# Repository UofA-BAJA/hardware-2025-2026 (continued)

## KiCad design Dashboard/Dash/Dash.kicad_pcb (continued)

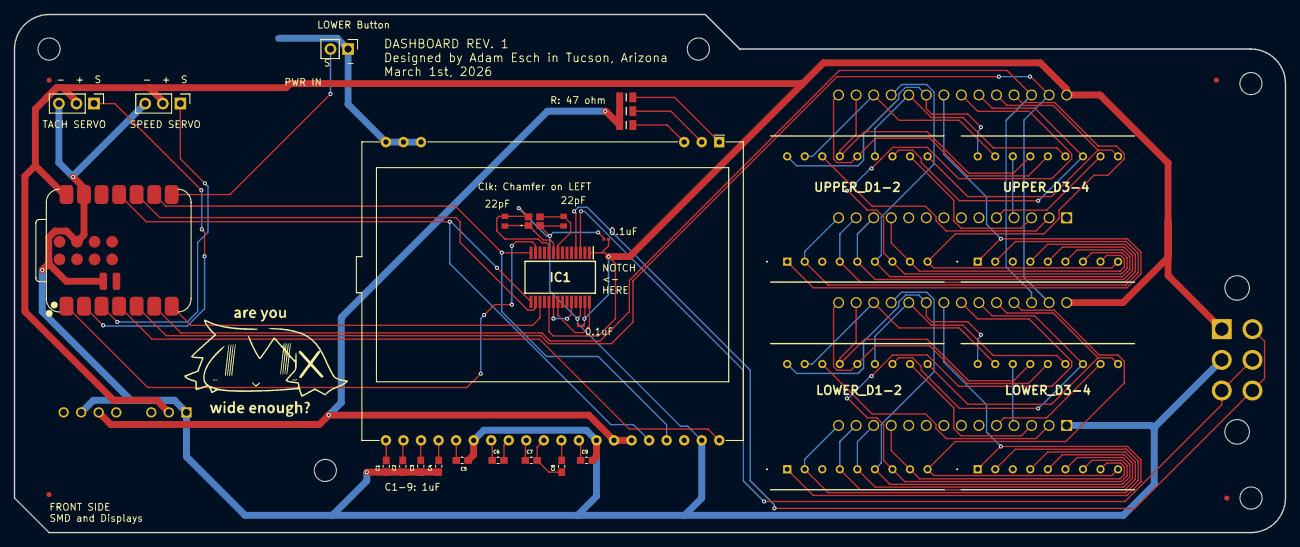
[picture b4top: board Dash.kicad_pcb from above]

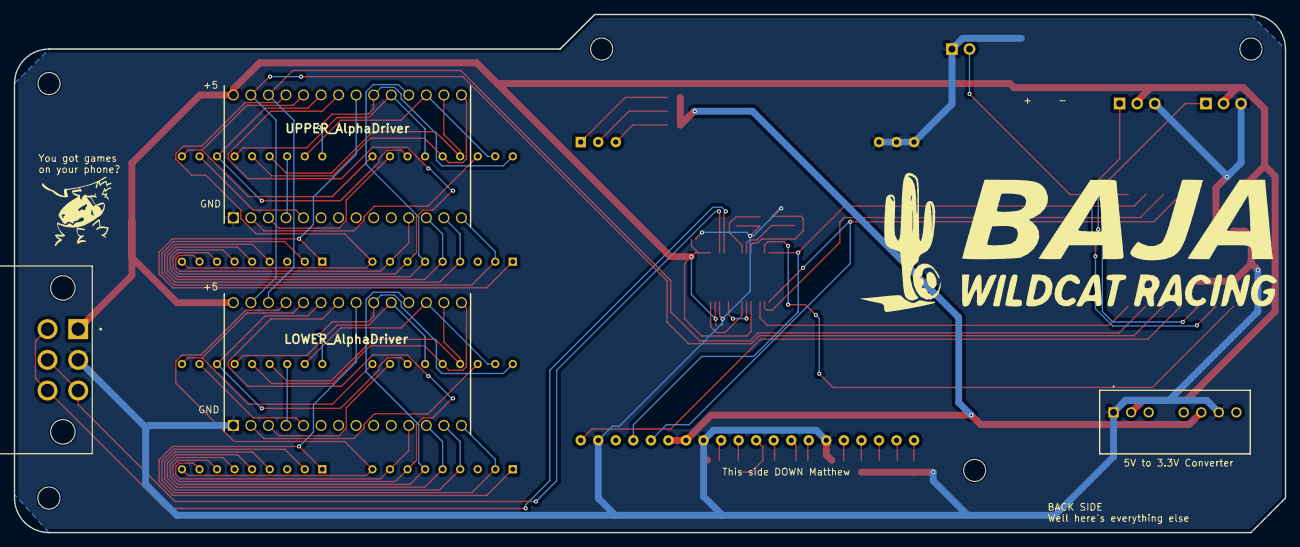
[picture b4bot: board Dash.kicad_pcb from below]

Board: 2 copper layers, 184.0 x 75.0 mm, 31 parts (4 on the bottom side), 72 nets.

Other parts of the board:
LOWER_AlphaDriver: Alphanumeric Driver LOWER; DIP1778W100P254L3556H630Q28N
UPPER_AlphaDriver: Alphanumeric Driver UPPER; DIP1778W100P254L3556H630Q28N

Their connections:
+5V: LOWER_AlphaDriver.28 (VDD), UPPER_AlphaDriver.28 (VDD); also elsewhere on the board
COM_Digit1_LOWER: LOWER_AlphaDriver.2 (C0); also elsewhere on the board
COM_Digit1_UPPER: UPPER_AlphaDriver.2 (C0); also elsewhere on the board
COM_Digit2_LOWER: LOWER_AlphaDriver.3 (C1); also elsewhere on the board
COM_Digit2_UPPER: UPPER_AlphaDriver.3 (C1); also elsewhere on the board
COM_Digit3_LOWER: LOWER_AlphaDriver.4 (C2); also elsewhere on the board
COM_Digit3_UPPER: UPPER_AlphaDriver.4 (C2); also elsewhere on the board
COM_Digit4_LOWER: LOWER_AlphaDriver.5 (C3); also elsewhere on the board
COM_Digit4_UPPER: UPPER_AlphaDriver.5 (C3); also elsewhere on the board
GND: LOWER_AlphaDriver.1 (GND), UPPER_AlphaDriver.1 (GND); also elsewhere on the board
ROW0_LOWER: LOWER_AlphaDriver.23 (A2); also elsewhere on the board
ROW0_UPPER: UPPER_AlphaDriver.23 (A2); also elsewhere on the board
ROW1_LOWER: LOWER_AlphaDriver.24 (A1); also elsewhere on the board
ROW1_UPPER: UPPER_AlphaDriver.24 (A1); also elsewhere on the board
ROW2_LOWER: LOWER_AlphaDriver.25 (A0); also elsewhere on the board
ROW2_UPPER: UPPER_AlphaDriver.25 (A0); also elsewhere on the board
ROW3_LOWER: LOWER_AlphaDriver.22 (A3); also elsewhere on the board
ROW3_UPPER: UPPER_AlphaDriver.22 (A3); also elsewhere on the board
ROW4_LOWER: LOWER_AlphaDriver.21 (A4); also elsewhere on the board
ROW4_UPPER: UPPER_AlphaDriver.21 (A4); also elsewhere on the board
ROW5_LOWER: LOWER_AlphaDriver.20 (A5); also elsewhere on the board
ROW5_UPPER: UPPER_AlphaDriver.20 (A5); also elsewhere on the board
ROW6_LOWER: LOWER_AlphaDriver.19 (A6); also elsewhere on the board
ROW6_UPPER: UPPER_AlphaDriver.19 (A6); also elsewhere on the board
ROW7_LOWER: LOWER_AlphaDriver.18 (A7); also elsewhere on the board
ROW7_UPPER: UPPER_AlphaDriver.18 (A7); also elsewhere on the board
ROW8_LOWER: LOWER_AlphaDriver.17 (A8); also elsewhere on the board
ROW8_UPPER: UPPER_AlphaDriver.17 (A8); also elsewhere on the board
ROW9_LOWER: LOWER_AlphaDriver.16 (A9); also elsewhere on the board
ROW9_UPPER: UPPER_AlphaDriver.16 (A9); also elsewhere on the board
ROW10_LOWER: LOWER_AlphaDriver.15 (A10); also elsewhere on the board
ROW10_UPPER: UPPER_AlphaDriver.15 (A10); also elsewhere on the board
ROW11_LOWER: LOWER_AlphaDriver.14 (A11); also elsewhere on the board
ROW11_UPPER: UPPER_AlphaDriver.14 (A11); also elsewhere on the board
ROW12_LOWER: LOWER_AlphaDriver.13 (A12); also elsewhere on the board
ROW12_UPPER: UPPER_AlphaDriver.13 (A12); also elsewhere on the board
ROW13_LOWER: LOWER_AlphaDriver.12 (A13); also elsewhere on the board
ROW13_UPPER: UPPER_AlphaDriver.12 (A13); also elsewhere on the board
ROW14_LOWER: LOWER_AlphaDriver.11 (A14); also elsewhere on the board
ROW14_UPPER: UPPER_AlphaDriver.11 (A14); also elsewhere on the board
SCL: LOWER_AlphaDriver.26 (SCL), UPPER_AlphaDriver.26 (SCL); also elsewhere on the board
SDA: LOWER_AlphaDriver.27 (SDA), UPPER_AlphaDriver.27 (SDA); also elsewhere on the board

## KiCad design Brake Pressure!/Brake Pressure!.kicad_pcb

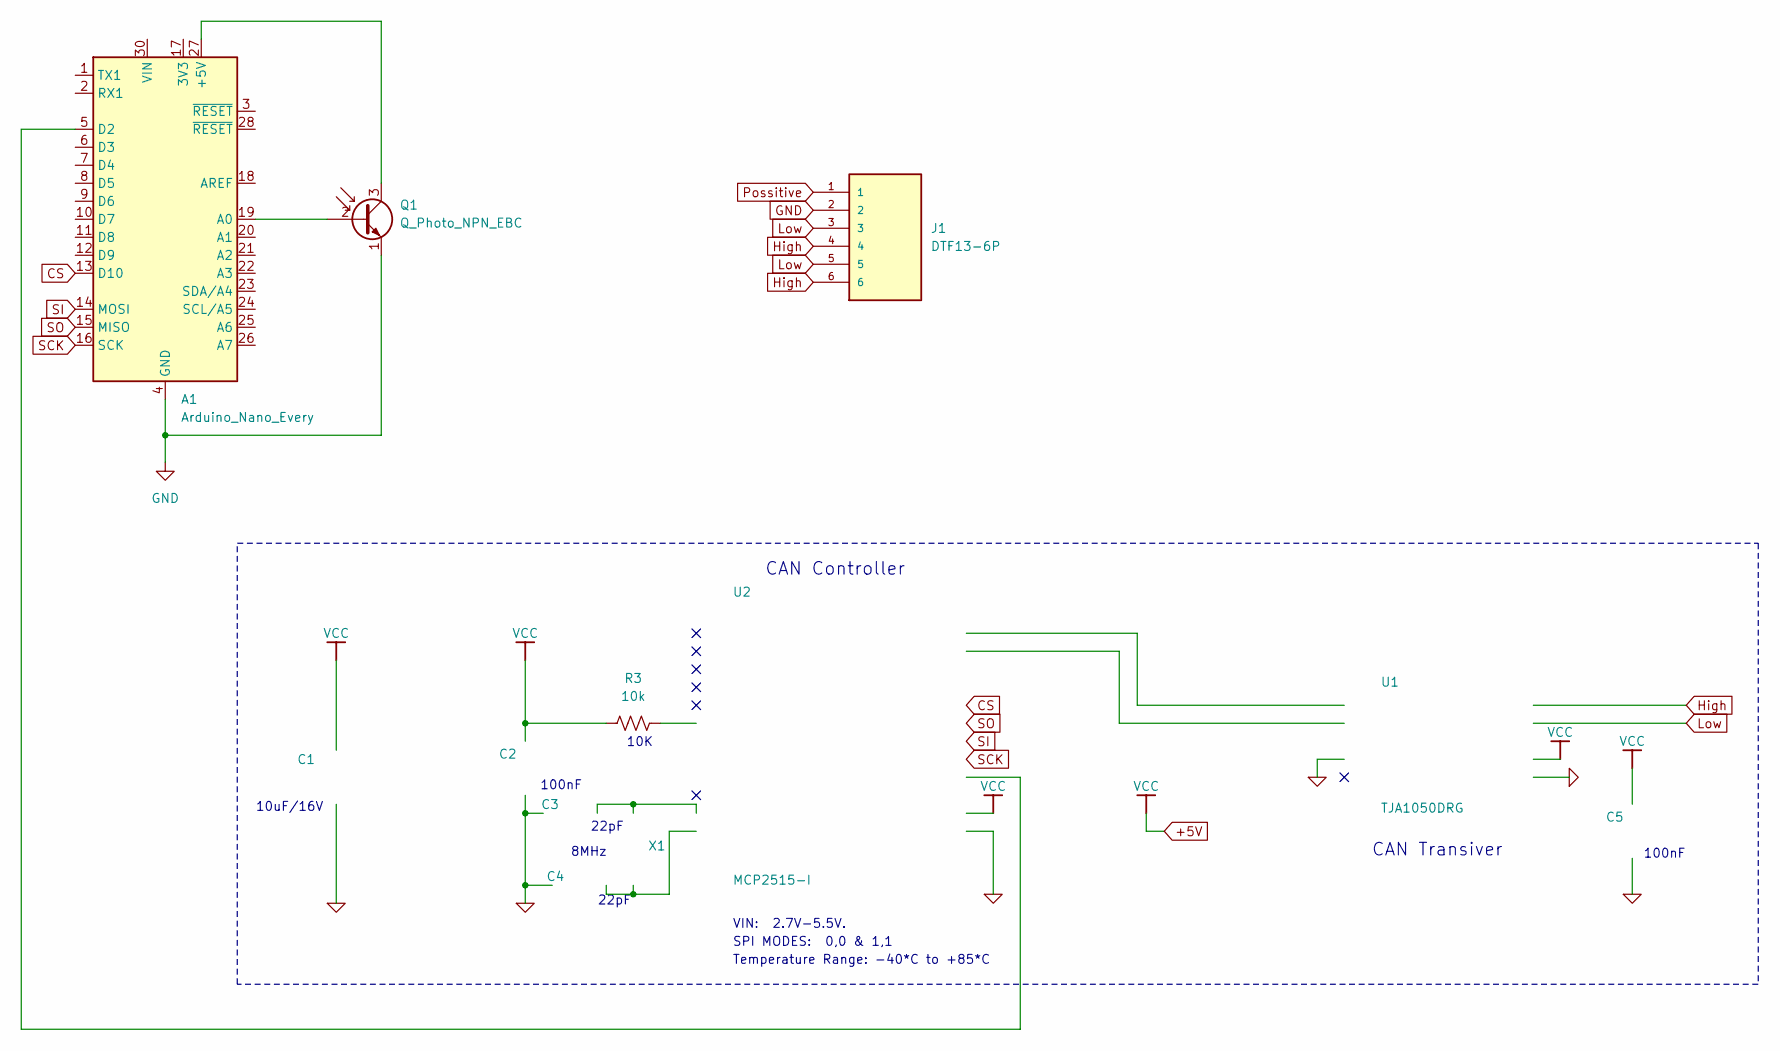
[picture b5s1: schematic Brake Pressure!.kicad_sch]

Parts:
A1: Arduino_Nano_Every; Arduino_Nano
C1: 10uF/16V; CP_EIA-1608-08_AVX-J
C2, C5: 100nF; C_0603_1608Metric; PART NUMBER C0603-N.C.
C3, C4: 22pF; C_0603_1608Metric; PART NUMBER C0603-N.C.
J1: DTF13-6P; TE_DTF13-6P; PARTREV B
Q1: Q_Photo_NPN_EBC; TO-3P-3_Vertical
R3: 10k; R_Axial_DIN0204_L3.6mm_D1.6mm_P7.62mm_Horizontal
U1: TJA1050DRG; SOIC-8_5.3x5.3mm_P1.27mm; MANUFACTURER PART TJA1050DRG; LCSC PART NAME TJA1050DRG
U2: MCP2515-I; SOIC-18W_7.5x11.6mm_P1.27mm; MANUFACTURER PART MCP2515-I; JLCPCB PART CLASS Extended Part
X1: 8MHz; Crystal_SMD_HC49-SD

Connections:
0: C1.2, C2.1, C3.2, C4.2, C5.1, U1.2 (GND), U1.8 (STB), U2.9 (VSS)
+5V: C1.1, C2.2, C5.2, R3.1, U1.3 (VCC), U2.18 (VDD)
CS: A1.13 (D10), U2.16 (~CS)
GND: A1.4 (GND), A1.29 (GND), J1.2, Q1.1 (E)
High: J1.4, J1.6, U1.7 (CANH)
Low: J1.3, J1.5, U1.6 (CANL)
unnamed: A1.27 (+5V), Q1.3 (C)
unnamed: A1.19 (A0), Q1.2 (B)
unnamed: A1.5 (D2), U2.12 (~INT)
unnamed: U1.4 (RXD), U2.2 (RXCAN)
unnamed: U1.1 (TXD), U2.1 (TXCAN)
unnamed: C4.1, U2.8 (OSC1), X1.1
unnamed: C3.1, U2.7 (OSC2), X1.2
unnamed: R3.2, U2.17 (~RESET)
Possitive: J1.1
SCK: A1.16 (SCK), U2.13 (SCK)
SI: A1.14 (MOSI), U2.14 (SI)
SO: A1.15 (MISO), U2.15 (SO)

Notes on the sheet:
CAN Transiver
22pF
100nF
VIN: 2.7V-5.5V.
CAN Controller
10K
Temperature Range: -40*C to +85*C
8MHz
10uF/16V
SPI MODES: 0,0 & 1,1

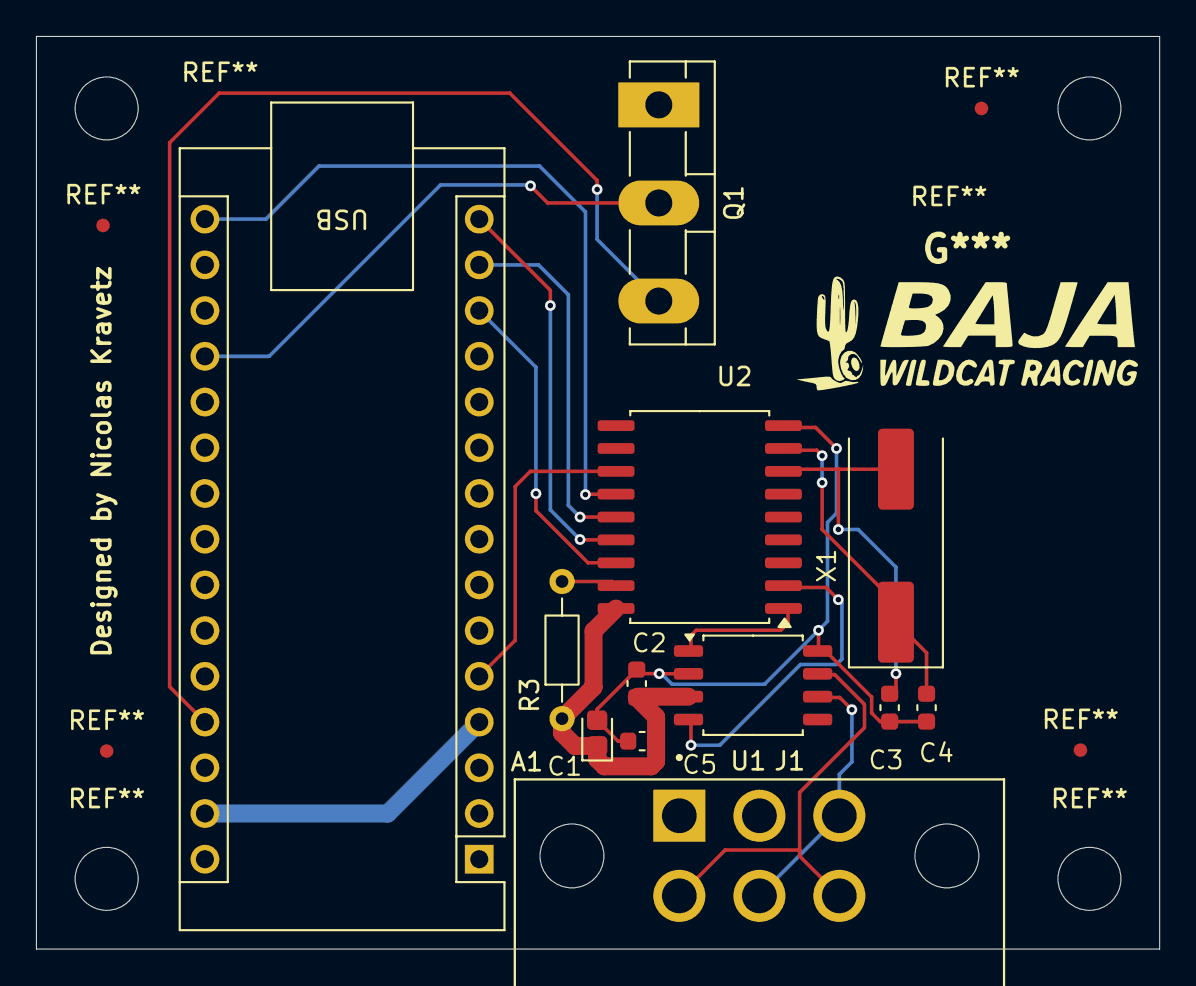
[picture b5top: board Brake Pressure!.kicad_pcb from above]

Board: 2 copper layers, 62.4 x 50.7 mm, 12 parts (0 on the bottom side), 17 nets.

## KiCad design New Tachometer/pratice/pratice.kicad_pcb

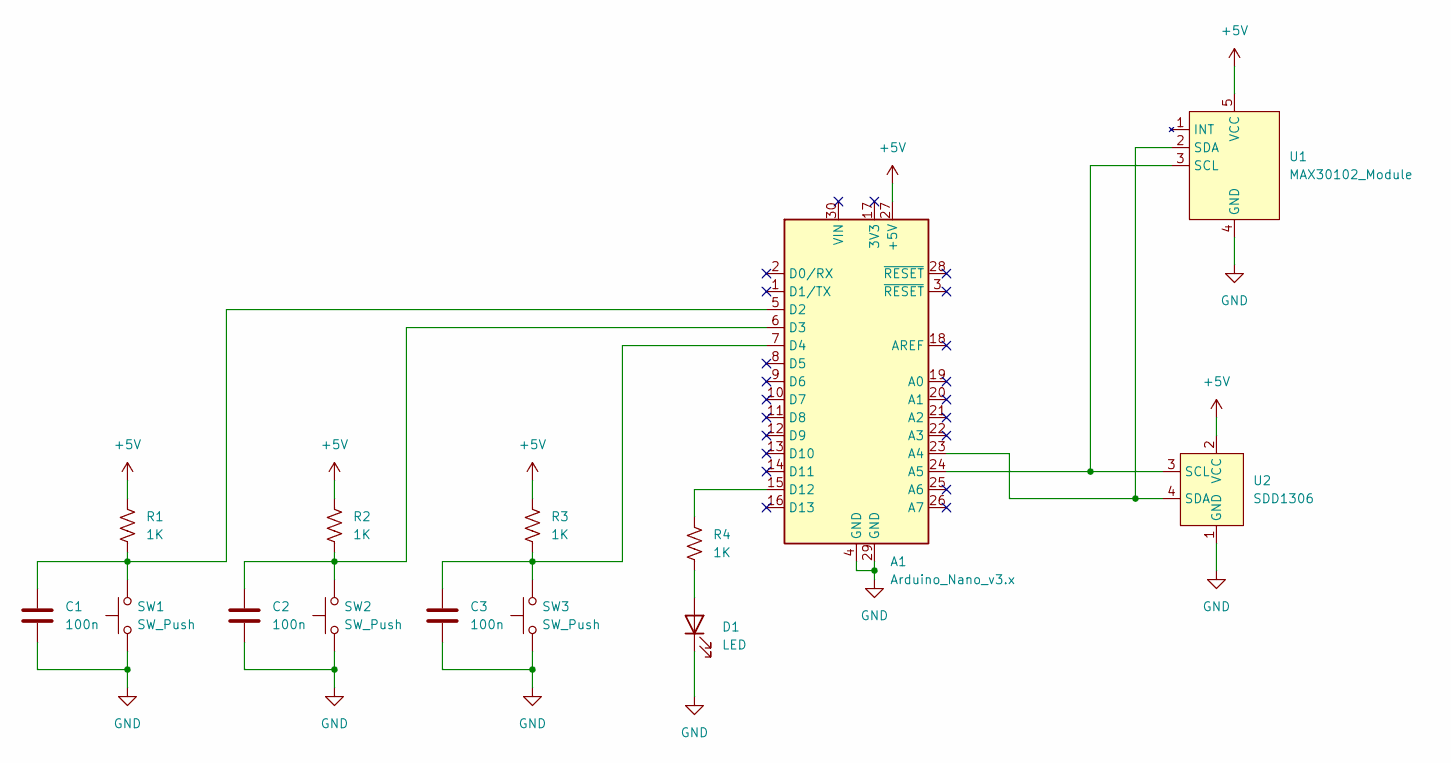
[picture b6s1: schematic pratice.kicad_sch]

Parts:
A1: Arduino_Nano_v3.x; Arduino_Nano
C1, C2, C3: 100n; C_Disc_D4.7mm_W2.5mm_P5.00mm
D1: LED; LED_D5.0mm
R1, R2, R3, R4: 1K; R_Axial_DIN0207_L6.3mm_D2.5mm_P7.62mm_Horizontal
SW1, SW2, SW3: SW_Push; SW_PUSH_6mm
U1: MAX30102_Module
U2: SDD1306; SSD1306

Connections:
+5V: A1.27 (+5V), R1.1, R2.1, R3.1, U1.5 (VCC), U2.2 (VCC)
GND: A1.4 (GND), A1.29 (GND), C1.2, C2.2, C3.2, D1.1 (K), SW1.1, SW2.1, SW3.1, U1.4 (GND), U2.1 (GND)
unnamed: A1.23 (A4), U1.2 (SDA), U2.4 (SDA)
unnamed: A1.24 (A5), U1.3 (SCL), U2.3 (SCL)
unnamed: A1.5 (D2), C1.1, R1.2, SW1.2
unnamed: A1.6 (D3), C2.1, R2.2, SW2.2
unnamed: A1.7 (D4), C3.1, R3.2, SW3.2
unnamed: A1.15 (D12), R4.1
unnamed: D1.2 (A), R4.2

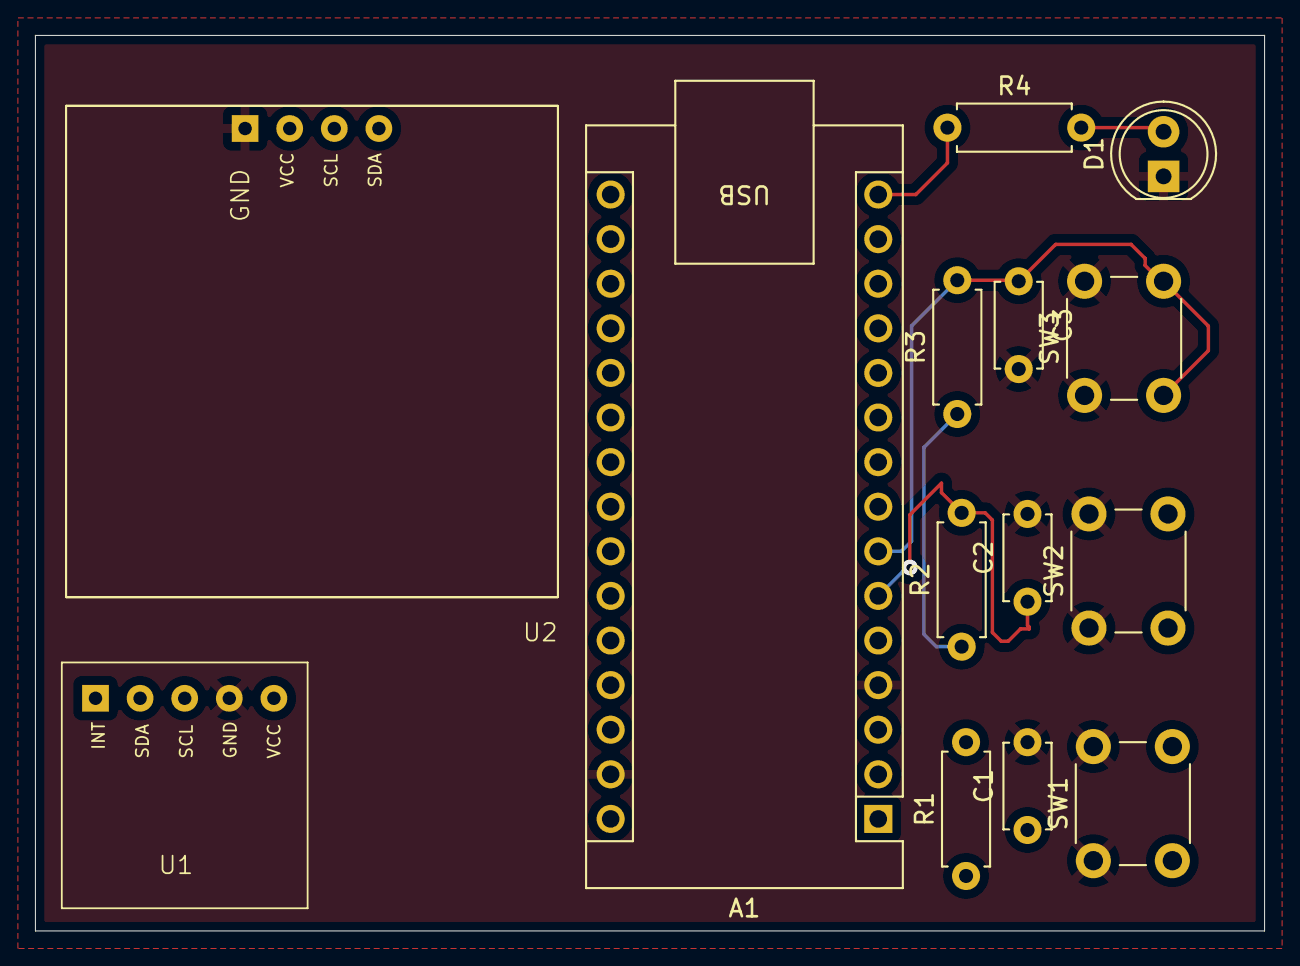
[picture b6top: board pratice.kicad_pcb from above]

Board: 4 copper layers, 70.0 x 51.0 mm, 14 parts (0 on the bottom side), 9 nets.

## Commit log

2025-12-06 new tachometer
2026-01-22 add main computer PCB
2026-01-22 need to align pinheader
2026-01-24 routing done
    still need to make can attachment holes bigger
2026-01-26 ready to submit
2026-02-02 Added Displacement Sensor
2026-02-28 Added Fiducial Points
2026-02-28 Updated Labels
2026-02-28 Updated Again
2026-02-28 brake pressure
2026-02-28 tachmeter
2026-02-28 Added Interrupt
2026-02-28 Little Change for Interupt
2026-02-28 Swapped upper button for CAN_INT
2026-02-28 Cleanup on SPI/I2C Traces
2026-02-28 Added Fiducial and Int
2026-03-02 tach
2026-03-02 Speedometer
2026-03-02 temp sensor
2026-03-02 Connected Can Bus to Arduino
2026-03-02 aw hell naw
2026-03-02 make new connection
2026-03-02 AAAAAAAAAA
2026-03-02 update stuff, fix error
2026-03-02 Add F points
2026-03-02 Fixed Shorting DRC Errors
2026-03-02 brake pressure done
2026-03-02 I swear the CAN_GND can be safely shorted to GND
2026-03-02 Fixed Schematic and Removed CAN_GND on CAN chip
2026-03-02 Fonts used on Dash
2026-03-28 start???
2026-04-09 workprogress
2026-04-09 Revert PCB (footprint nonsense)
    This reverts commit 10dbf7cf734bf138f5810b545ad3c613d1decc14.
2026-04-09 Revert "Revert PCB (footprint nonsense)"
    This reverts commit 552c51d2d454395f20641a831b1a19d05ce70707.
2026-04-09 Revert only PCB this time
    This reverts some of commit 10dbf7cf734bf138f5810b545ad3c613d1decc14.
2026-04-09 PCB KNOWN GOOD
2026-04-09 rev 2 almost done
2026-04-11 Rev 2, DRC pass
2026-04-14 Fixed the speedometer silly
